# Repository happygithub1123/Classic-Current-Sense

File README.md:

# Classic Current Sense

经典低端电流检测电路：使用 **0.1 Ω 采样电阻 + OPA333 运放**，检测 0～2 A 单向直流电流。包含完整 KiCad 10 原理图、已布线的双层 PCB、制造文件及检查报告。

| 参数 | 数值 |
| --- | --- |
| 运放供电 | +5 V |
| 标称增益 | 16 |
| 理想输出 | 1.6 V/A；2 A 对应 3.2 V |
| 采样电阻 | 0.1 Ω，1 W，1%，2512 |
| PCB 尺寸 | 45 × 35 mm，双层，1.6 mm 板厚 |
| 主电流走线 | 2 mm 宽 |
| 输出滤波 | 1 kΩ + 100 nF，RC 截止频率约 1.59 kHz |

## 打开项目

使用 KiCad 10 打开 [Classic_Current_Sense.kicad_pro](Classic_Current_Sense.kicad_pro)。

- [原理图](Classic_Current_Sense.kicad_sch)
- [PCB](Classic_Current_Sense.kicad_pcb)
- [制造文件：Gerber 与钻孔](manufacturing/)
- [物料表](BOM.csv)
- [顶层贴片坐标](placement.csv)
- [详细接线、布局与使用说明](使用说明.md)

J1-1 接负载负极，J1-2 接负载电源负极；电源正极直接接负载正极。J2 的 1/2/3 脚分别为 +5 V、GND、VOUT。

## 验证

2026-11-16，KiCad 10.0.8：

- [ERC](ERC_final.json)：0 违规。
- [DRC](DRC_final.rpt)：0 错误、0 警告、0 未连接焊盘，包含原理图一致性检查。

以上是设计文件检查，尚未进行打样、实物温升和精度测试。近零电流时存在输出摆幅与失调限制；3.2 V 为满量程标称值，连接 3.3 V ADC 时应考虑容差、过流和输入保护。具体工艺与器件选型见使用说明。

## 设计工具

本工程通过本地部署的 [KiCAD-MCP-Server](https://github.com/mixelpixx/KiCAD-MCP-Server) v2.9.0 与 KiCad 10.0.8 创建。PCB 编辑使用实时 IPC，使布局、走线和铺铜变化直接显示在 KiCad 编辑器中。

KiCAD-MCP-Server 是独立的上游项目。本仓库存放本电流检测工程；本地安装程序、Python 环境及个人 Codex 配置不在仓库中。

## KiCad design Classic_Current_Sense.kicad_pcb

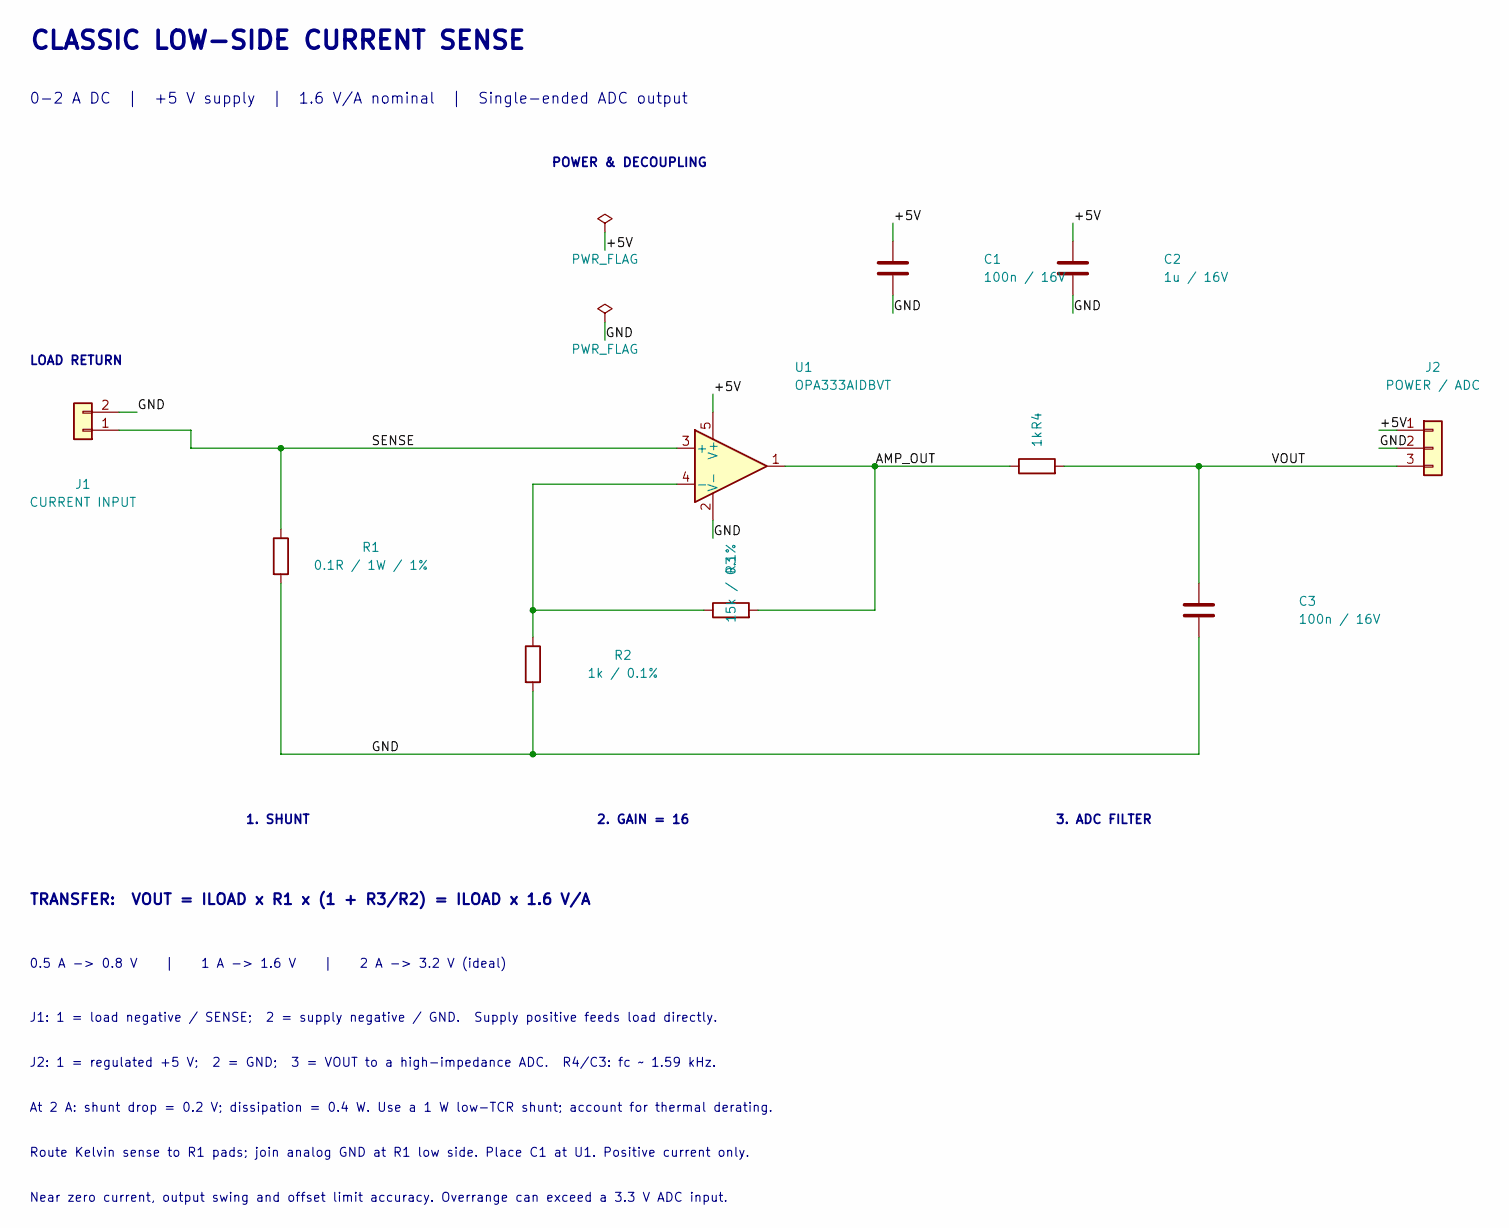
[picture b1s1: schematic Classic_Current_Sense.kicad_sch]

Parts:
C1, C3: 100n / 16V; C_0603_1608Metric
C2: 1u / 16V; C_0603_1608Metric
J1: CURRENT INPUT; TerminalBlock_Phoenix_MKDS-1,5-2_1x02_P5.00mm_Horizontal
J2: POWER / ADC; PinHeader_1x03_P2.54mm_Vertical
R1: 0.1R / 1W / 1%; R_2512_6332Metric; Tolerance 1%
R2: 1k / 0.1%; R_0603_1608Metric; Tolerance 0.1%
R3: 15k / 0.1%; R_0603_1608Metric; Tolerance 0.1%
R4: 1k; R_0603_1608Metric
U1: OPA333AIDBVT; SOT-23-5; MPN OPA333AIDBVT

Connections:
/+5V: C1.1, C2.1, J2.1, U1.5 (V+)
/AMP_OUT: R3.2, R4.1, U1.1
/GND: C1.2, C2.2, C3.2, J1.2, J2.2, R1.2, R2.2, U1.2 (V-)
/SENSE: J1.1, R1.1, U1.3 (+)
/VOUT: C3.1, J2.3, R4.2
unnamed: R2.1, R3.1, U1.4 (-)

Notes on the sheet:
CLASSIC LOW-SIDE CURRENT SENSE
0-2 A DC | +5 V supply | 1.6 V/A nominal | Single-ended ADC output
POWER & DECOUPLING
LOAD RETURN
1. SHUNT
2. GAIN = 16
3. ADC FILTER
TRANSFER: VOUT = ILOAD x R1 x (1 + R3/R2) = ILOAD x 1.6 V/A
0.5 A -> 0.8 V | 1 A -> 1.6 V | 2 A -> 3.2 V (ideal)
J1: 1 = load negative / SENSE; 2 = supply negative / GND. Supply positive feeds load directly.
J2: 1 = regulated +5 V; 2 = GND; 3 = VOUT to a high-impedance ADC. R4/C3: fc ~ 1.59 kHz.
At 2 A: shunt drop = 0.2 V; dissipation = 0.4 W. Use a 1 W low-TCR shunt; account for thermal derating.
Route Kelvin sense to R1 pads; join analog GND at R1 low side. Place C1 at U1. Positive current only.
Near zero current, output swing and offset limit accuracy. Overrange can exceed a 3.3 V ADC input.

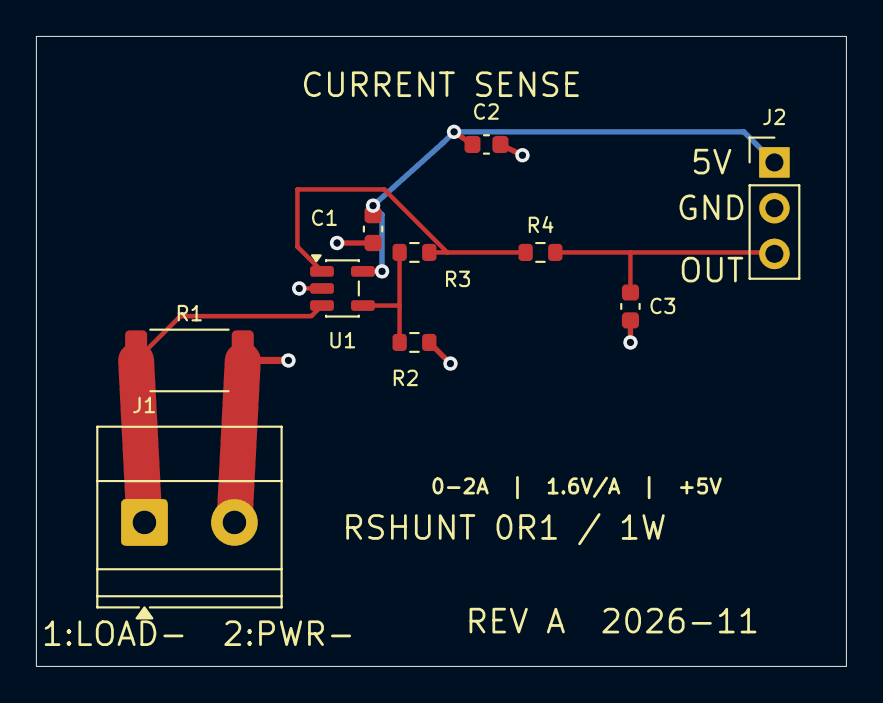
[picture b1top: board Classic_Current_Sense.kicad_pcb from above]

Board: 2 copper layers, 45.0 x 35.0 mm, 10 parts (0 on the bottom side), 6 nets.

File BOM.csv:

"Reference","Value","Footprint","Manufacturer","MPN","Power","Tolerance"
"C1","100n / 16V","Capacitor_SMD:C_0603_1608Metric","","","",""
"C2","1u / 16V","Capacitor_SMD:C_0603_1608Metric","","","",""
"C3","100n / 16V","Capacitor_SMD:C_0603_1608Metric","","","",""
"J1","CURRENT INPUT","TerminalBlock_Phoenix:TerminalBlock_Phoenix_MKDS-1,5-2_1x02_P5.00mm_Horizontal","","","",""
"J2","POWER / ADC","Connector_PinHeader_2.54mm:PinHeader_1x03_P2.54mm_Vertical","","","",""
"R1","0.1R / 1W / 1%","Resistor_SMD:R_2512_6332Metric","","","1 W","1%"
"R2","1k / 0.1%","Resistor_SMD:R_0603_1608Metric","","","","0.1%"
"R3","15k / 0.1%","Resistor_SMD:R_0603_1608Metric","","","","0.1%"
"R4","1k","Resistor_SMD:R_0603_1608Metric","","","",""
"U1","OPA333AIDBVT","Package_TO_SOT_SMD:SOT-23-5","Texas Instruments","OPA333AIDBVT","",""
